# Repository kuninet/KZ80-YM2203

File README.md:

# KZ80マイコン(SBC80系)用 YM2203 FM音源ボード

## 概要
- KZ80マイコン(SBC80系)用 YM2203 FM音源ボードです。
- SBC8080バスに接続できます。
- 出力端子(イヤホンジャック)からアンプ経由に接続してください。

## 注意
- 試作確認しているところなので、間違いがあったらご指摘ください。

## ライセンス
- MITライセンスで公開します。

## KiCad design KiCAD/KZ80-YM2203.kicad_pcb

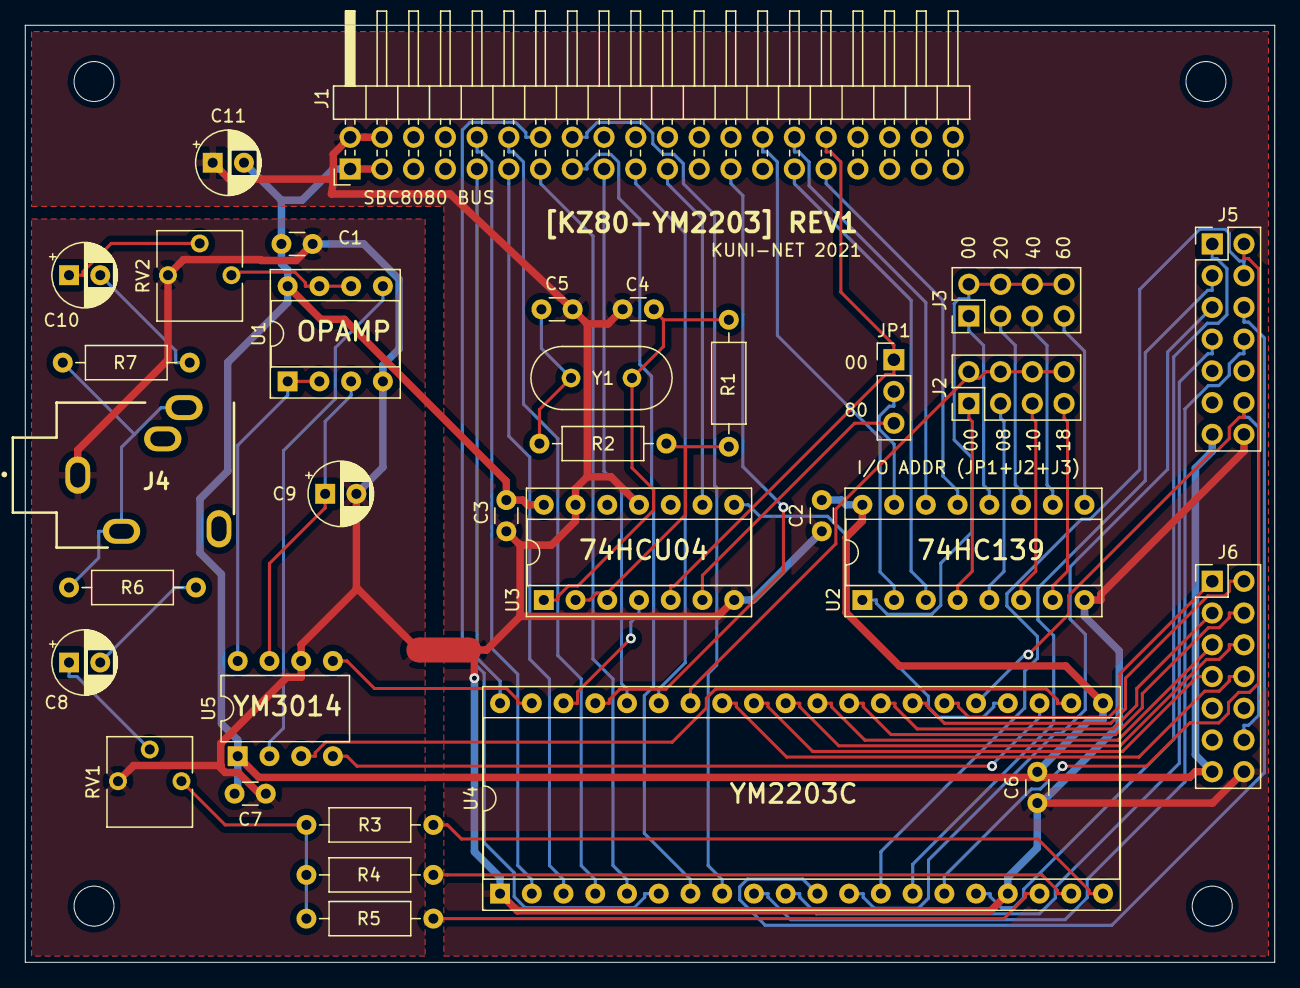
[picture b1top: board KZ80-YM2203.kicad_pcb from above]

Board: 2 copper layers, 100.0 x 75.0 mm, 38 parts (0 on the bottom side), 70 nets.

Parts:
C1, C2, C3, C6, C7: 0.1u; C_Disc_D3.0mm_W1.6mm_P2.50mm
C4, C5: 22p; C_Disc_D3.0mm_W1.6mm_P2.50mm
C8, C9, C10, C11: 10u; CP_Radial_D5.0mm_P2.50mm
H1, H2, H3, H4: MountingHole; MountingHole_3.2mm_M3
J1: SBC8080 BUS; PinHeader_2x20_P2.54mm_Horizontal
J2, J3: AD-JP1; PinHeader_2x04_P2.54mm_Vertical
J4: Audio-Jack; AJ-1780
J5: A-CON; PinHeader_2x07_P2.54mm_Vertical
J6: B-CON; PinHeader_2x07_P2.54mm_Vertical
JP1: A7 JP; PinHeader_1x03_P2.54mm_Vertical
NT1: Net-Tie_2; NetTie-2_SMD_Pad2.0mm
R1: 1M; R_Axial_DIN0207_L6.3mm_D2.5mm_P10.16mm_Horizontal
R2, R3, R4, R5, R6, R7: 1k; R_Axial_DIN0207_L6.3mm_D2.5mm_P10.16mm_Horizontal
RV1: 1k; Potentiometer_Vishay_T73YP_Vertical
RV2: 10k; Potentiometer_Vishay_T73YP_Vertical
U1: NJM5532DD; DIP-8_W7.62mm_Socket
U2: 74LS139; DIP-16_W7.62mm_Socket
U3: 74HCU04; DIP-14_W7.62mm_Socket
U4: YM2203; DIP-40_W15.24mm_Socket
U5: YM3014B; DIP-8_W7.62mm
Y1: 3.579545MHz; Crystal_HC49-U_Vertical

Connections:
/A0: J1.25, U4.37
/A3: J1.28, U2.2
/A4: J1.29, U2.3
/A5: J1.30, U2.14
/A6: J1.31, U2.13
/A7: J1.32, JP1.1, U3.5
/D0: J1.9, U4.40
/D1: J1.10, U4.2
/D2: J1.11, U4.3
/D3: J1.12, U4.4
/D4: J1.13, U4.5
/D5: J1.14, U4.6
/D6: J1.15, U4.7
/D7: J1.16, U4.8
/IOA0: J5.1, U4.16
/IOA1: J5.2, U4.15
/IOA2: J5.3, U4.14
/IOA3: J5.4, U4.13
/IOA4: J5.5, U4.12
/IOA5: J5.6, U4.11
/IOA6: J5.7, U4.10
/IOA7: J5.8, U4.9
/IOB0: J6.1, U4.26
/IOB1: J6.2, U4.27
/IOB2: J6.3, U4.28
/IOB3: J6.4, U4.29
/IOB4: J6.5, U4.30
/IOB5: J6.6, U4.31
/IOB6: J6.7, U4.32
/IOB7: J6.8, U4.33
/RES: J1.21, U3.9
/~IORD: J1.17, U4.36
/~IOWR: J1.19, U4.35
/~IRQ: J5.12, J6.12, U4.25
/~RES: U3.8, U4.24
GND: C2.1, C3.1, C4.2, C5.2, C6.1, C11.1, J1.2, J1.4, J5.14, J6.14, NT1.2, U2.8, U3.7, U3.11, U3.13, U4.1, U4.17
GNDA: C1.1, C7.1, C9.2, J4.1, NT1.1, RV1.3, RV2.3, U1.4, U5.6
unnamed: C4.1, R1.2, U3.1, Y1.1
unnamed: C5.1, R2.2, Y1.2
unnamed: C8.1, RV1.2
unnamed: C8.2, R6.2
unnamed: C9.1, U1.3, U5.7
unnamed: C10.1, RV2.2
unnamed: C10.2, R7.2
unnamed: J2.1, U2.4
unnamed: J2.2, J2.4, J2.6, J2.8, U4.34
unnamed: J2.3, U2.5
unnamed: J2.5, U2.6
unnamed: J2.7, U2.7
unnamed: J3.1, U2.12
unnamed: J3.2, J3.4, J3.6, J3.8, U2.1
unnamed: J3.3, U2.11
unnamed: J3.5, U2.10
unnamed: J3.7, U2.9
unnamed: J4.2, J4.5, R6.1, R7.1
unnamed: JP1.2, U2.15
unnamed: JP1.3, U3.6
unnamed: R1.1, R2.1, U3.2, U3.3
unnamed: R3.1, R4.1, R5.1, RV1.1
unnamed: R3.2, U4.20
unnamed: R4.2, U4.19
unnamed: R5.2, U4.18
unnamed: RV2.1, U1.6, U1.7
unnamed: U1.1, U1.2, U5.8
unnamed: U1.5, U5.2
unnamed: U3.4, U4.38
unnamed: U4.22, U5.3
unnamed: U4.23, U5.4
unnamed: U4.39, U5.5
VCC: C1.2, C2.2, C3.2, C6.2, C7.2, C11.2, J1.1, J1.3, J5.13, J6.13, U1.8, U2.16, U3.14, U4.21, U5.1

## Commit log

2020-11-01 init commit
2020-11-01 Create LICENSE
2020-11-01 回路図追加
2020-11-01 パス見直し
2020-12-02 YM2203 VGMプレーヤー試作
2020-12-06 回路図 間違いなど修正。出力段に抵抗器装着
2020-12-07 回路図修正版イメージ差し替え
2020-12-26 CP/M-80版 VGMPLAY作成
2021-03-20 基板パターン検討・ガーバーデータ出力
2021-03-25 パターンを基板縁から離す対応を実施・ガーバー出力
